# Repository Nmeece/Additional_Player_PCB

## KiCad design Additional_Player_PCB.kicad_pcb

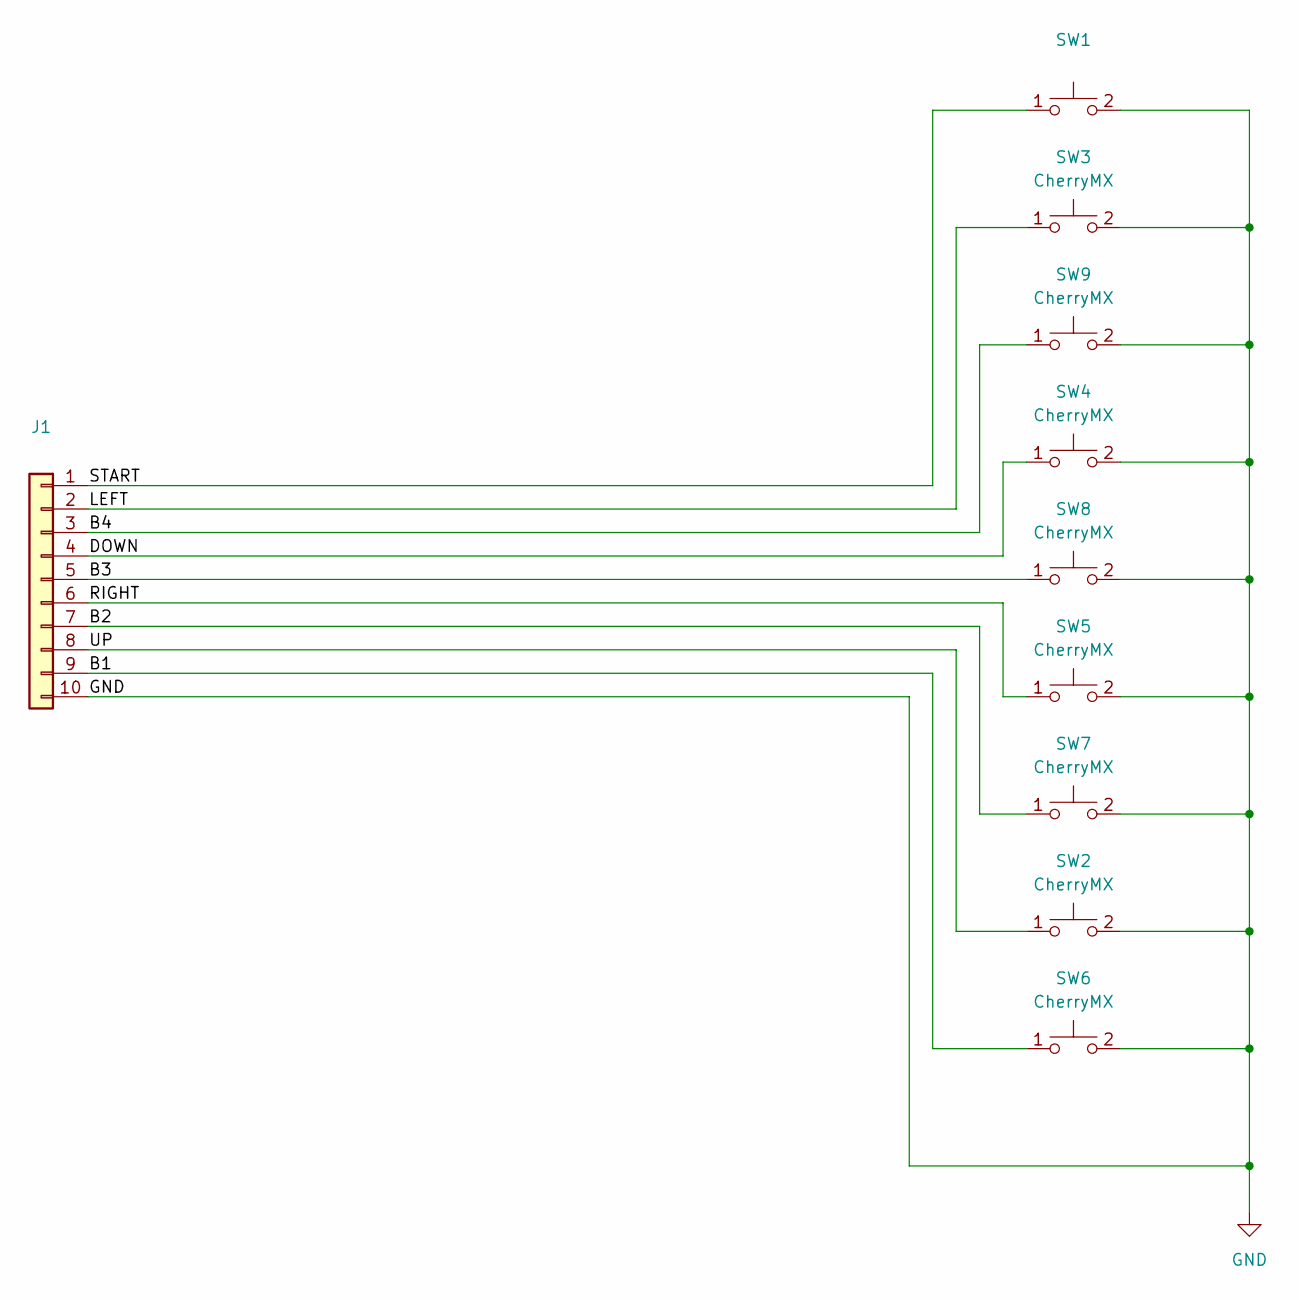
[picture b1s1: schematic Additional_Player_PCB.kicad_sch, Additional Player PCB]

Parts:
J1: (no value)
SW1: (no value)
SW2, SW3, SW4, SW5, SW6, SW7, SW8, SW9: CherryMX; SW_Cherry_MX_1.00u_PCB

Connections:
/B1: J1.9, SW6.1
/B2: J1.7, SW7.1
/B3: J1.5, SW8.1
/B4: J1.3, SW9.1
/DOWN: J1.4, SW4.1
/LEFT: J1.2, SW3.1
/RIGHT: J1.6, SW5.1
/START: J1.1, SW1.1
/UP: J1.8, SW2.1
GND: J1.10, SW1.2, SW2.2, SW3.2, SW4.2, SW5.2, SW6.2, SW7.2, SW8.2, SW9.2

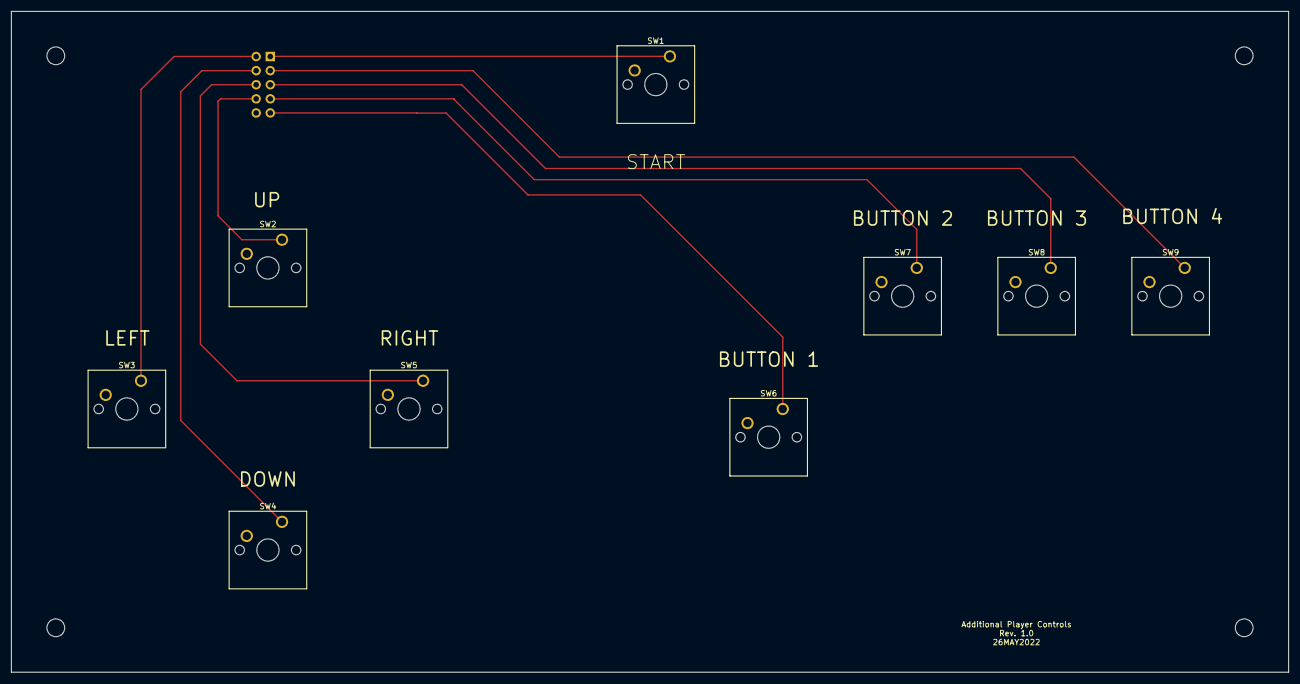
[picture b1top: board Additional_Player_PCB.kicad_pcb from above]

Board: 2 copper layers, 230.0 x 119.0 mm, 14 parts (1 on the bottom side), 10 nets.

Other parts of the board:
MH: MountingHole_3.2mm_M3
MH#2, MH#3, MH#4: MountingHole_3.2mm_M3

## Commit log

2022-05-28 Initial Commit
    *slaps roof of repo* You can fit so many PCB designs in the bad boy.
2022-05-28 Integrated Library
    Created a library consisting of only parts found on the board.
2022-05-28 Integrated Library but for real this time
    Same as the last one
2022-05-28 oops all libraries
    Whats a fella gotta do to have pretty 3D models on his board?
2022-05-28 Net Names Added
    Didn't realize that annotations didn't function as official net names. Fixed now.
2022-05-28 Models and
    Models
2022-05-28 Board Art Resources Added
    It's called art.
2022-06-09 Correct J1 connector
    Mil vs. MM, what's the deal?
2022-06-09 Silkscreen Correction
    Somehow managed to nudge silkscreen label without realizing. A big goof on my part. Fixed now tho.
